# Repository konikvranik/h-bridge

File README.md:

# h-bridge
Try to achieve safe h-bridge with bi-stable circuit flipping by high current (motor overloaded) and signal from micro controller

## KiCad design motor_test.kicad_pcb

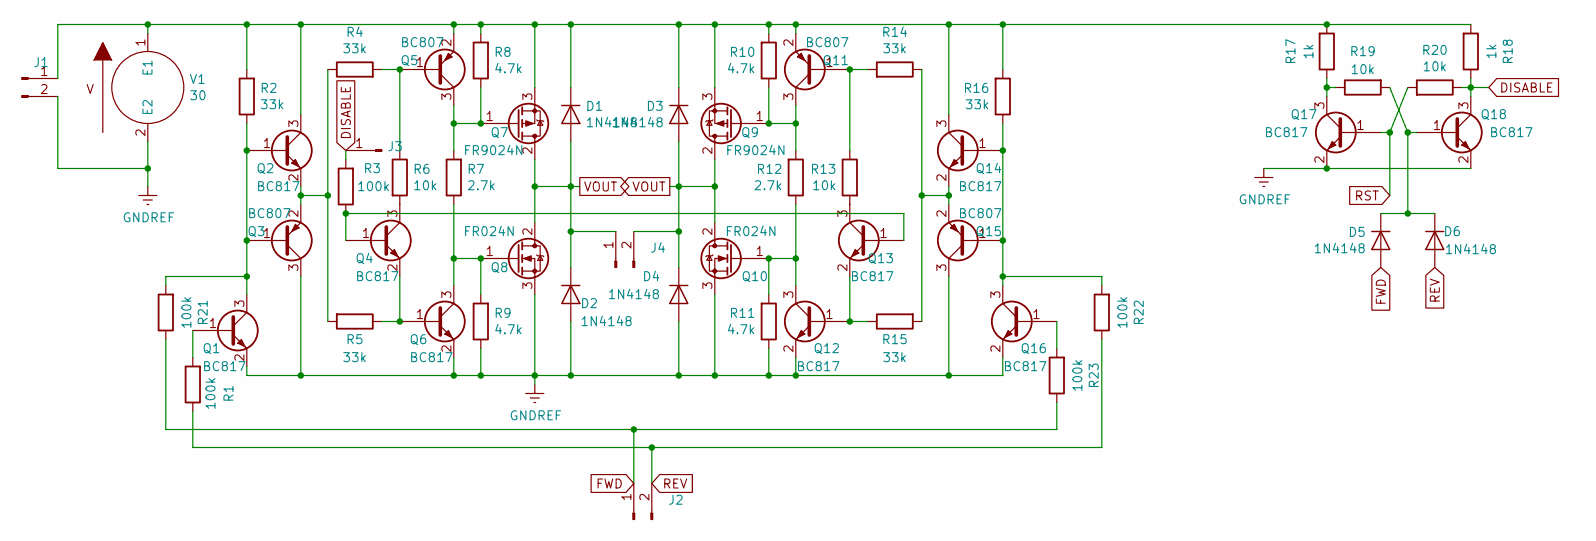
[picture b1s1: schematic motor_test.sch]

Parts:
D1, D2, D3, D4, D5, D6: 1N4148; D_DO-35_SOD27_P7.62mm_Horizontal
J1, J2, J4: Conn_01x02_Male; PinHeader_1x02_P2.54mm_Vertical
J3: Conn_01x01_Male; PinHeader_1x01_P2.54mm_Vertical
Q1, Q2, Q4, Q6, Q12, Q13, Q14, Q16, Q17, Q18: BC817; SOT-23
Q3, Q5, Q11, Q15: BC807; SOT-23
Q7, Q9: FR9024N; TO-252-3_TabPin2
Q8, Q10: FR024N; TO-252-3_TabPin2
R1, R3, R21, R22, R23: 100k; R_1206_3216Metric
R2, R4, R5, R14, R15, R16: 33k; R_1206_3216Metric
R6, R13, R19, R20: 10k; R_1206_3216Metric
R7, R12: 2.7k; R_1206_3216Metric
R8, R9, R10, R11: 4.7k; R_1206_3216Metric
R17, R18: 1k; R_1206_3216Metric
V1: 30

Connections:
DISABLE: J3.1, Q18.3 (C), R3.2, R18.1, R20.1
FWD: D5.2 (A), J2.1, R21.1, R23.1
GNDREF: D2.2 (A), D4.2 (A), J1.2, Q1.2 (E), Q3.3 (C), Q6.2 (E), Q8.3 (S), Q10.3 (S), Q12.2 (E), Q15.3 (C), Q16.2 (E), Q17.2 (E), Q18.2 (E), R9.1, R11.1, V1.2 (E2)
unnamed: D1.1 (K), D3.1 (K), J1.1, Q2.3 (C), Q5.2 (E), Q7.3 (S), Q9.3 (S), Q11.2 (E), Q14.3 (C), R2.2, R8.2, R10.2, R16.2, R17.2, R18.2, V1.1 (E1)
unnamed: D5.1 (K), D6.1 (K), Q18.1 (B), R19.2
unnamed: Q1.1 (B), R1.2
unnamed: Q1.3 (C), Q2.1 (B), Q3.1 (B), R2.1, R21.2
unnamed: Q2.2 (E), Q3.2 (E), R4.1, R5.2
unnamed: Q4.2 (E), Q6.1 (B), R5.1
unnamed: Q4.3 (C), R6.2
unnamed: Q5.1 (B), R4.2, R6.1
unnamed: Q5.3 (C), Q7.1 (G), R7.2, R8.1
unnamed: Q6.3 (C), Q8.1 (G), R7.1, R9.2
unnamed: Q10.1 (G), Q12.3 (C), R11.2, R12.1
unnamed: Q11.1 (B), R13.1, R14.2
unnamed: Q9.1 (G), Q11.3 (C), R10.1, R12.2
unnamed: Q12.1 (B), Q13.2 (E), R15.1
unnamed: Q4.1 (B), Q13.1 (B), R3.1
unnamed: Q13.3 (C), R13.2
unnamed: Q14.1 (B), Q15.1 (B), Q16.3 (C), R16.1, R22.2
unnamed: Q14.2 (E), Q15.2 (E), R14.1, R15.2
unnamed: Q16.1 (B), R23.2
unnamed: Q17.3 (C), R17.1, R19.1
REV: D6.2 (A), J2.2, R1.1, R22.1
RST: Q17.1 (B), R20.2
VOUT: D1.2 (A), D2.1 (K), D3.2 (A), D4.1 (K), J4.1, J4.2, Q7.2 (D), Q8.2 (D), Q9.2 (D), Q10.2 (D)

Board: 2 copper layers, 52 parts (0 on the bottom side), 26 nets, no tracks yet.

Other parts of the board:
J2#2: Conn_01x01_Male; PinHeader_1x01_P2.54mm_Vertical

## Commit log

2020-02-18 1 motor bridges
2020-02-18 bistable
2020-02-22 h-bridge
2020-02-23 nightly
